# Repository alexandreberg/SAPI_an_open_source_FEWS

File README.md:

# SAPI — Sistema de Alerta Prévio de Inundações

**Flood Early Warning System** — a low-cost, open-source, LoRa-based platform for water-level
and rainfall monitoring, machine-learning flood forecasting and multi-channel alerts,
developed and validated as a Master's dissertation project (IFSC, Florianópolis, Brazil).

## Read this README in your language / Leia este README no seu idioma

| Language | File |
|----------|------|
| 🇬🇧 English | **[README-en.md](README-en.md)** |
| 🇧🇷 Português | **[README-pt.md](README-pt.md)** |

> **Note / Nota** — The code, comments and most technical documentation in this repository
> are in **English**; the README and some documents in `docs/` are also in **Portuguese**,
> the language of the dissertation.
>
> O código, os comentários e a maior parte da documentação técnica deste repositório estão
> em **inglês**; o README e alguns documentos em `docs/` estão também em **português**, o
> idioma da dissertação.

## Quick links / Links rápidos

- Releases (firmware, models, hardware, web interface):
  <https://github.com/alexandreberg/SAPI_an_open_source_FEWS/releases>
- Project specification / Especificação do projeto: [`docs/system-overview.md`](docs/system-overview.md)
- Changelog: [`CHANGELOG.md`](CHANGELOG.md)
- Predictive models / Modelos preditivos:
  [`predictive-models/`](predictive-models/README.md)
- How this repository was built / Como este repositório foi construído:
  [`docs/PROVENANCE.md`](docs/PROVENANCE.md)

## License / Licença

Software: [AGPL-3.0-or-later](LICENSE) · Hardware (`hardware/`):
[CERN-OHL-S-2.0](LICENSES/CERN-OHL-S-2.0.txt) · Third-party credits / Créditos: [`NOTICE`](NOTICE)

Copyright (C) 2024–2026 Alexandre Nuernberg.

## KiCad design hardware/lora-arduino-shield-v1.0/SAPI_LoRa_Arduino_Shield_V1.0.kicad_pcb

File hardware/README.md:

# Hardware — KiCad projects

KiCad 9 projects of the two custom shields used by the SAPI stations. Both are
fabrication-ready (gerbers in `gerber_to_order/`) and licensed under
[CERN-OHL-S-2.0](../LICENSES/CERN-OHL-S-2.0.txt).

| Project | Release | What it does |
|---------|---------|--------------|
| [`morpho-shield-v1.2/`](morpho-shield-v1.2/) | `shield-morpho-v1.2.0` | ST Morpho interface board: tipping-bucket rain-gauge pulse counting, serial and trigger/echo ultrasonic sensor interfaces (US-100, HC-SR04, AJ-SR04M), I²C sensor bus (SHT20, BMP280), ADC for solar-panel and battery voltages, ST-Link connector, switched 3.3 V/5 V rails, 5 spare GPIOs |
| [`lora-arduino-shield-v1.0/`](lora-arduino-shield-v1.0/) | `shield-lora-arduino-v1.0.0` | Arduino-footprint radio shield for RFM69HC and LilyGo LoRa32 modules (any frequency; SAPI uses 915 MHz), with a debug LED that can be disabled for low power, a reset button and reconfigurable GPIOs |

## Git LFS and the 3D models

The 3D models (`*.step`, `*.stp`, `*.stl`, `*.wrl`, and zipped models) are stored in
**Git LFS**, ~0.9 GB in total. To clone without them:

```bash
GIT_LFS_SKIP_SMUDGE=1 git clone https://github.com/alexandreberg/SAPI_an_open_source_FEWS.git
```

KiCad opens the projects without the models; only the 3D viewer needs them. Each release
also has the complete project, models included, as a `.tar.gz` attachment.

## Third-party content

The SAPI design files (schematics, layouts, gerbers, BOM) are the author's work. The
projects also contain material **not** authored here, which keeps its original terms and
is not covered by the CERN-OHL-S licence:

- **3D models** (80 files per project) downloaded from CAD-sharing sites — folders named
  `*.snapshot.N` follow their download naming — made in SolidWorks, CATIA, FreeCAD,
  PRO/ENGINEER, the ASCON kernel and KiCad StepUp. Among them: the STM32 BluePill model,
  BME280/BMP280 modules, an SW868 antenna, 2.54 mm jumpers and pin headers, tactile and
  push switches, an optocoupler.
- **Symbol and footprint libraries** from SnapEDA and Digi-Key (`Project_Libraries/`,
  `Libraries/`).
- **Datasheets** of the 74HC166, CD4020BC, CD4040BEE4 and TIL133
  (`morpho-shield-v1.2/datasheets/`).

Their licences were not individually verified. If you are a rights holder and want a file
removed, please open an issue.

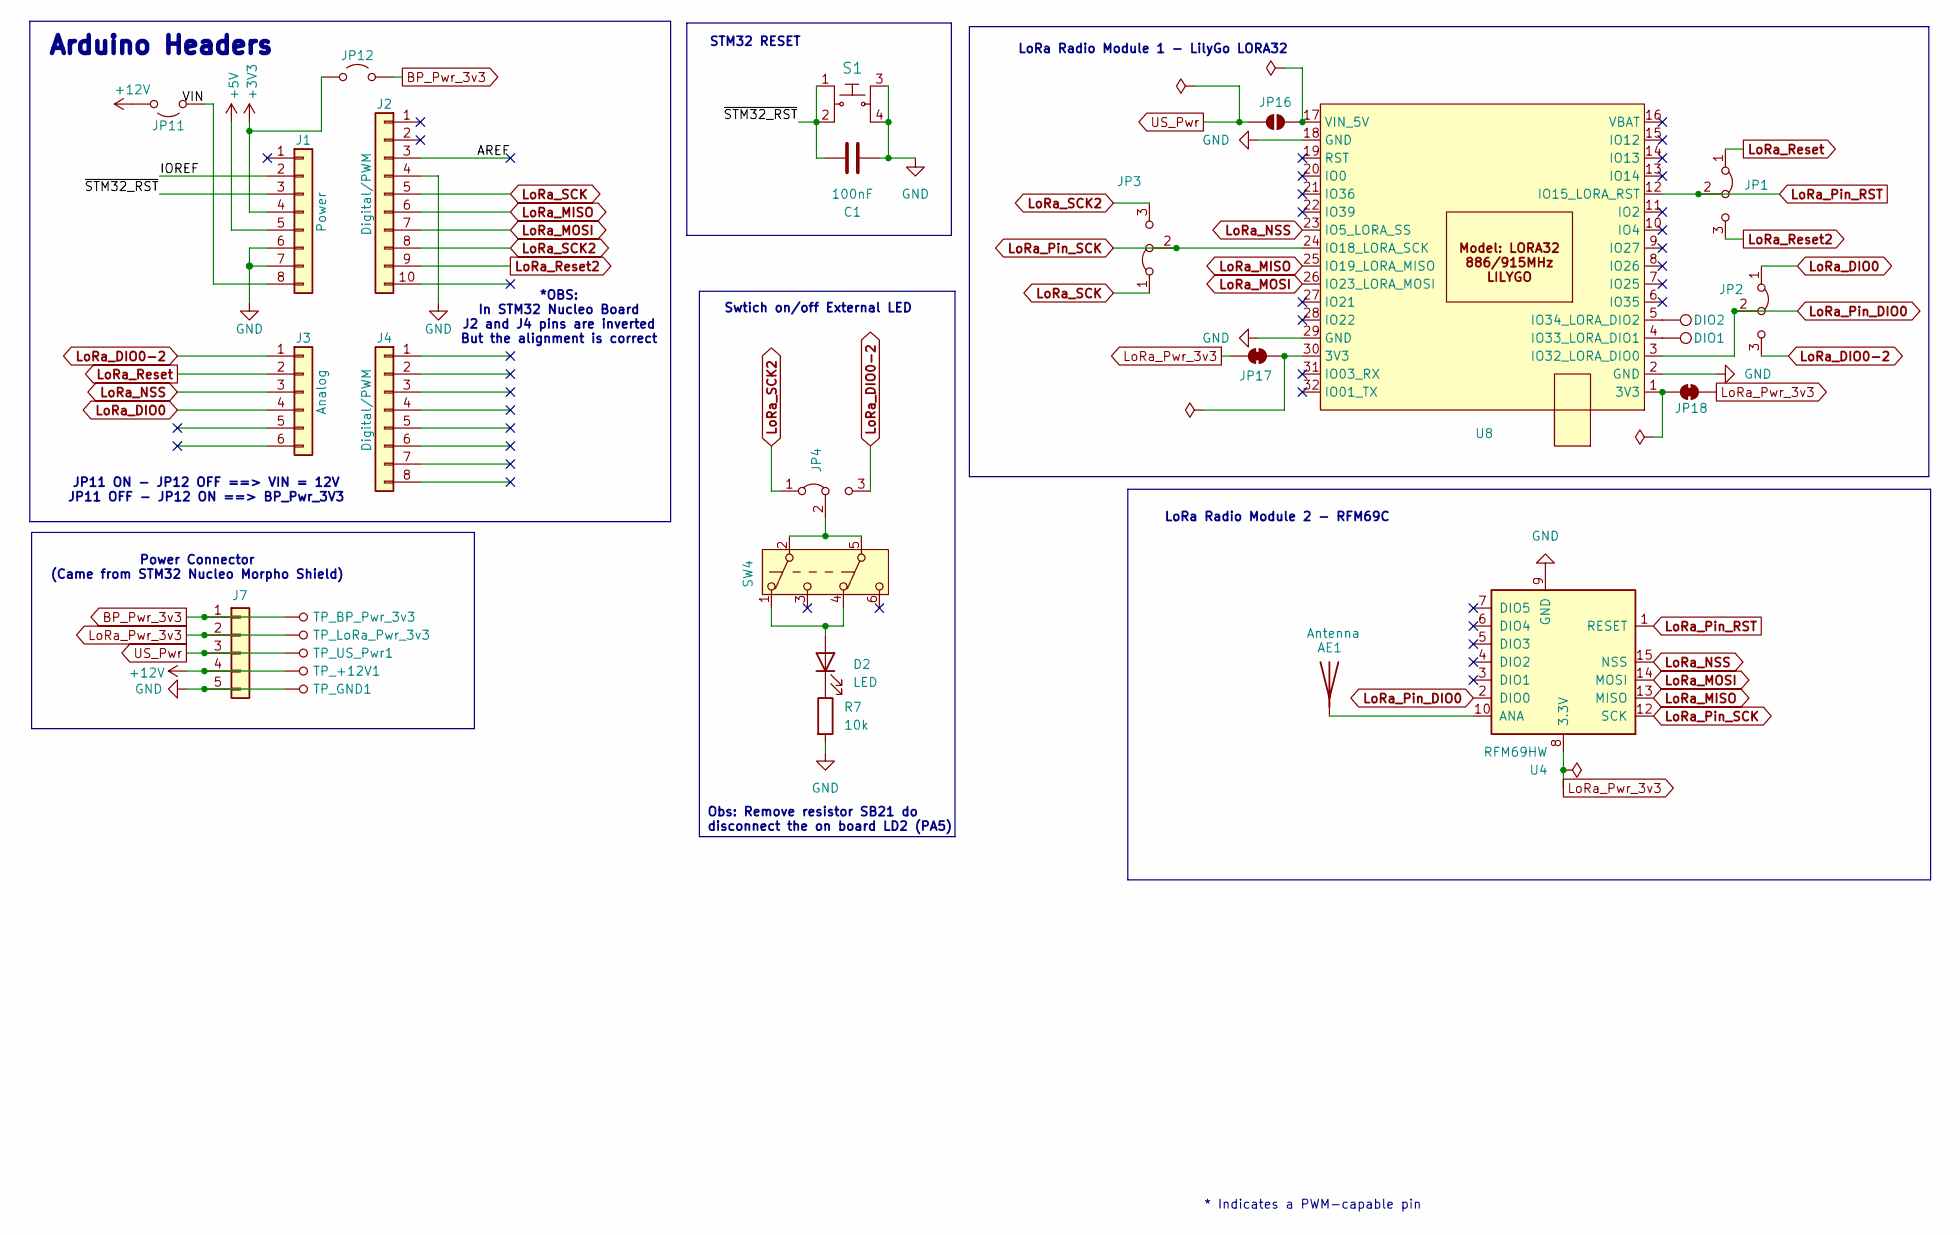
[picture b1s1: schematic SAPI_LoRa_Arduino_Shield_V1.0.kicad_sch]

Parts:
AE1: Antenna; ilha3d_LORA_Antenna
C1: 100nF; C_Disc_D5.1mm_W3.2mm_P5.00mm
D2: LED; LED_D3.0mm
J1: Power; PinHeader_1x08_P2.54mm_Vertical
J2: Digital/PWM; PinHeader_1x10_P2.54mm_Vertical
J3: Analog; PinHeader_1x06_P2.54mm_Vertical
J4: Digital/PWM; PinHeader_1x08_P2.54mm_Vertical
J7: Power; PinHeader_1x05_P2.54mm_Horizontal
JP1, JP4: LoRa_RST; Jumper_3Pins_SPDT_ilha3d
JP2: LoRa_DIO0; Jumper_3Pins_SPDT_ilha3d
JP3: LoRa_SCK; Jumper_3Pins_SPDT_ilha3d
JP11, JP12: Jumper_2_Open; PinHeader_1x02_P2.54mm_Vertical
JP16: SolderJumper_2_Open; SolderJumper-2_P1.3mm_Open_RoundedPad1.0x1.5mm
JP17, JP18: SolderJumper_2_Bridged; SolderJumper-2_P1.3mm_Bridged_RoundedPad1.0x1.5mm
R7: 10k; R_Axial_DIN0207_L6.3mm_D2.5mm_P7.62mm_Horizontal
S1: ilha3d_push_button_6x6; ilha3d_Switch_Tactile_THT_6x6mm; MPN 1825910-6; Digi-Key_PN 450-1650-ND
SW4: SW_Push_DPDT; SW_Push_2P2T_Toggle_CK_PVA2OAH5xxxxxxV2
TP21: DIO1; TestPoint_Pad_2.0x2.0mm
TP22: DIO2; TestPoint_Pad_2.0x2.0mm
TP_+12V1: +12V; Test_Point_D1.02mm; MPN 5000; Digi-Key_PN 36-5000-ND
TP_BP_Pwr_3v3: BP_Pwr_3v3; Test_Point_D1.02mm; MPN 5000; Digi-Key_PN 36-5000-ND
TP_GND1: GND; Test_Point_D1.02mm; MPN 5000; Digi-Key_PN 36-5000-ND
TP_LoRa_Pwr_3v3: LoRa_Pwr_3v3; Test_Point_D1.02mm; MPN 5000; Digi-Key_PN 36-5000-ND
TP_US_Pwr1: US_PwR; Test_Point_D1.02mm; MPN 5000; Digi-Key_PN 36-5000-ND
U4: RFM69HW; HOPERF_RFM69HW
U8: Ilha3d_LiLyGO_LORA32_LORA_XY

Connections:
+3V3: J1.4, JP12.1 (A)
+5V: J1.5
+12V: J7.4, JP11.2 (B), TP_+12V1.1
/ ~STM32_RST: C1.1, J1.3, S1.1, S1.2
/AREF: J2.3
/IOREF: J1.2
/VIN: J1.8, JP11.1 (A)
BP_Pwr_3v3: J7.1, JP12.2 (B), TP_BP_Pwr_3v3.1
GND: C1.2, J1.6, J1.7, J2.4, J7.5, R7.2, S1.3, S1.4, TP_GND1.1, U4.9 (GND), U4.11 (GND), U8.2 (GND), U8.18 (GND), U8.29 (GND)
LoRa_DIO0: J3.4, JP2.1 (A)
LoRa_DIO0-2: J3.1, JP2.3 (B), JP4.3 (B)
LoRa_MISO: J2.6, U4.13 (MISO), U8.25 (IO19_LORA_MISO)
LoRa_MOSI: J2.7, U4.14 (MOSI), U8.26 (IO23_LORA_MOSI)
LoRa_NSS: J3.3, U4.15 (NSS), U8.23 (IO5_LORA_SS)
LoRa_Pin_DIO0: JP2.2 (C), U4.2 (DIO0), U8.3 (IO32_LORA_DIO0)
LoRa_Pin_RST: JP1.2 (C), U4.1 (RESET), U8.12 (IO15_LORA_RST)
LoRa_Pin_SCK: JP3.2 (C), U4.12 (SCK), U8.24 (IO18_LORA_SCK)
LoRa_Pwr_3v3: J7.2, JP17.2 (B), JP18.1 (A), TP_LoRa_Pwr_3v3.1, U4.8 (3.3V)
LoRa_Reset: J3.2, JP1.1 (A)
LoRa_Reset2: J2.9, JP1.3 (B)
LoRa_SCK: J2.5, JP3.1 (A)
LoRa_SCK2: J2.8, JP3.3 (B), JP4.1 (A)
unnamed: AE1.1 (A), U4.10 (ANA)
unnamed: D2.2 (A), SW4.1 (A), SW4.4 (A)
unnamed: D2.1 (K), R7.1
unnamed: JP4.2 (C), SW4.2 (B), SW4.5 (B)
unnamed: JP16.1 (A), U8.17 (VIN_5V)
unnamed: JP17.1 (A), U8.30 (3V3)
unnamed: JP18.2 (B), U8.1 (3V3)
unnamed: TP21.1, U8.4 (IO33_LORA_DIO1)
unnamed: TP22.1, U8.5 (IO34_LORA_DIO2)
US_Pwr: J7.3, JP16.2 (B), TP_US_Pwr1.1

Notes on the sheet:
Obs: Remove resistor SB21 do disconnect the on board LD2 (PA5)
*OBS: In STM32 Nucleo Board J2 and J4 pins are inverted But the alignment is correct
Swtich on/off External LED
LoRa Radio Module 2 - RFM69C
Arduino Headers
JP11 ON - JP12 OFF ==> VIN = 12V JP11 OFF - JP12 ON ==> BP_Pwr_3V3
* Indicates a PWM-capable pin
LoRa Radio Module 1 - LilyGo LORA32
STM32 RESET
Power Connector (Came from STM32 Nucleo Morpho Shield)

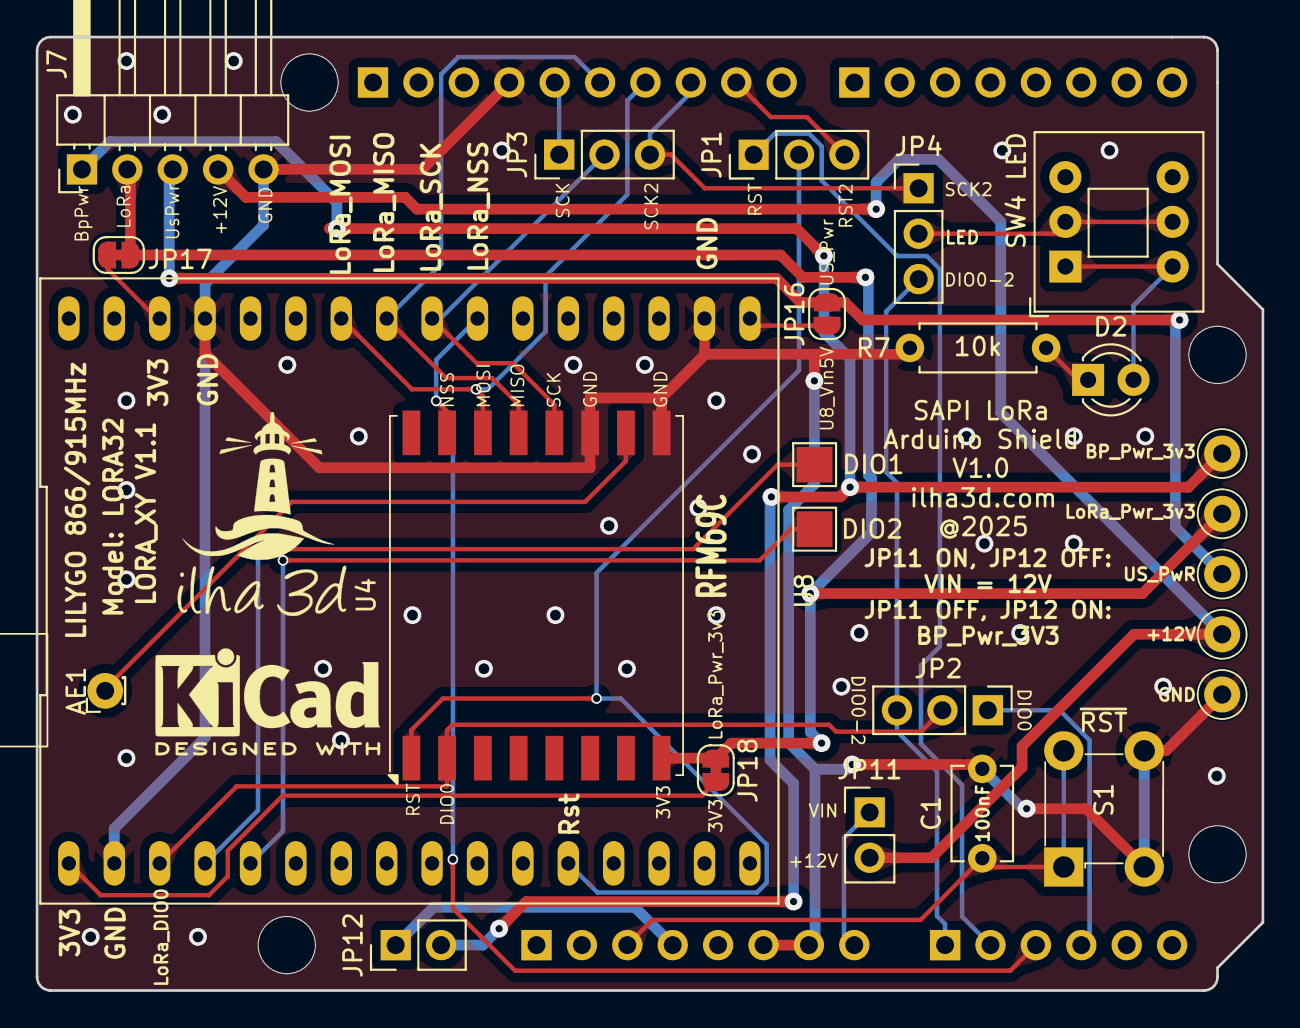
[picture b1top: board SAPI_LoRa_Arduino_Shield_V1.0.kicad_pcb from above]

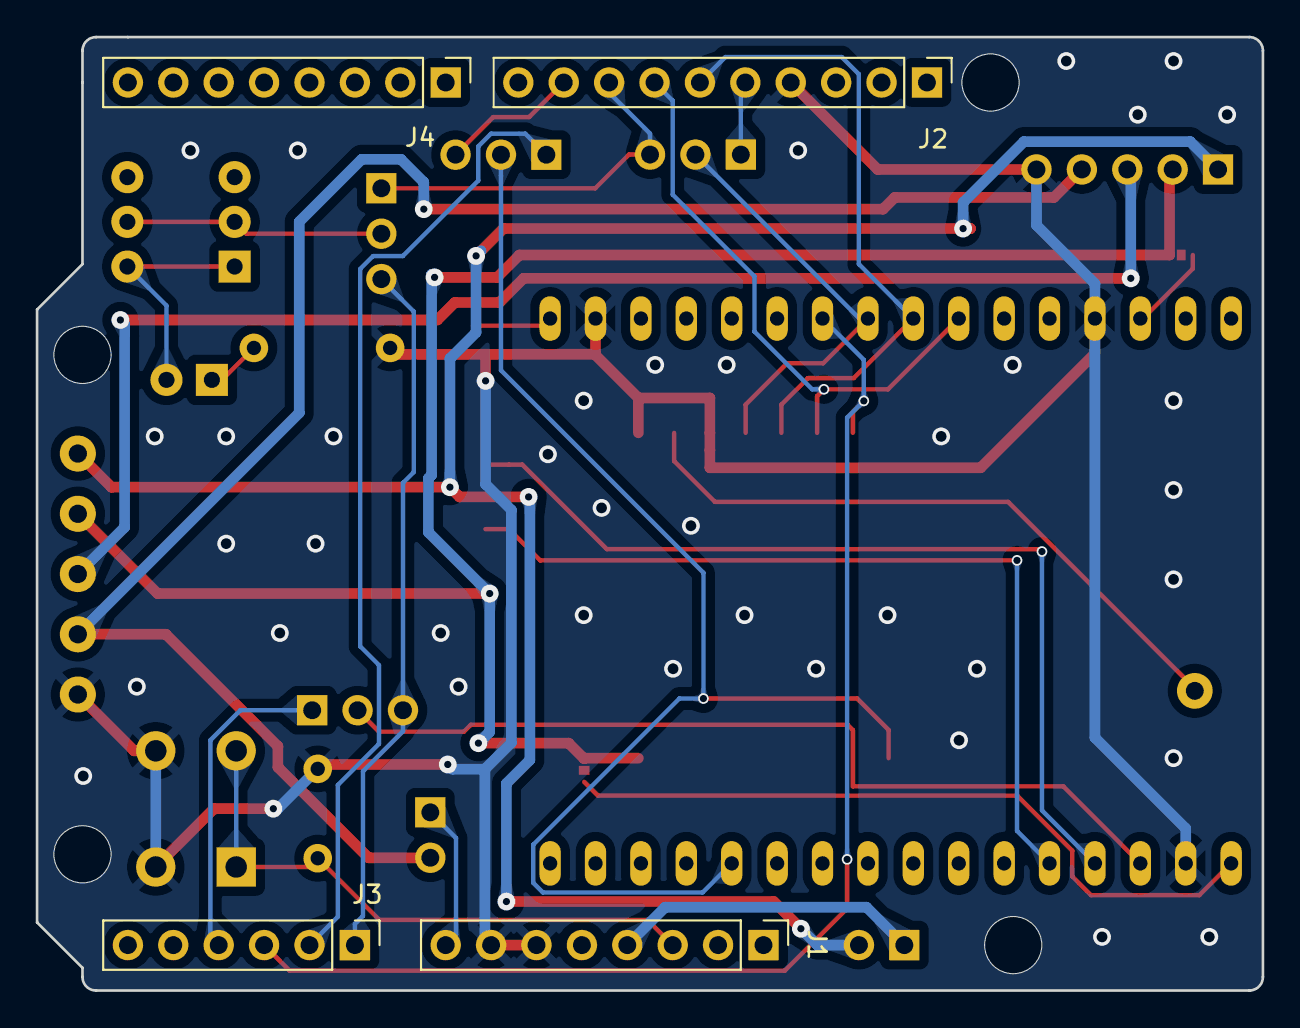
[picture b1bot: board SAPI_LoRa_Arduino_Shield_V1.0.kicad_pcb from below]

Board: 2 copper layers, 68.6 x 53.3 mm, 33 parts (4 on the bottom side), 29 nets.

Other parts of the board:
MH1, MH2, MH3, MH4: MountingHole_3.2mm

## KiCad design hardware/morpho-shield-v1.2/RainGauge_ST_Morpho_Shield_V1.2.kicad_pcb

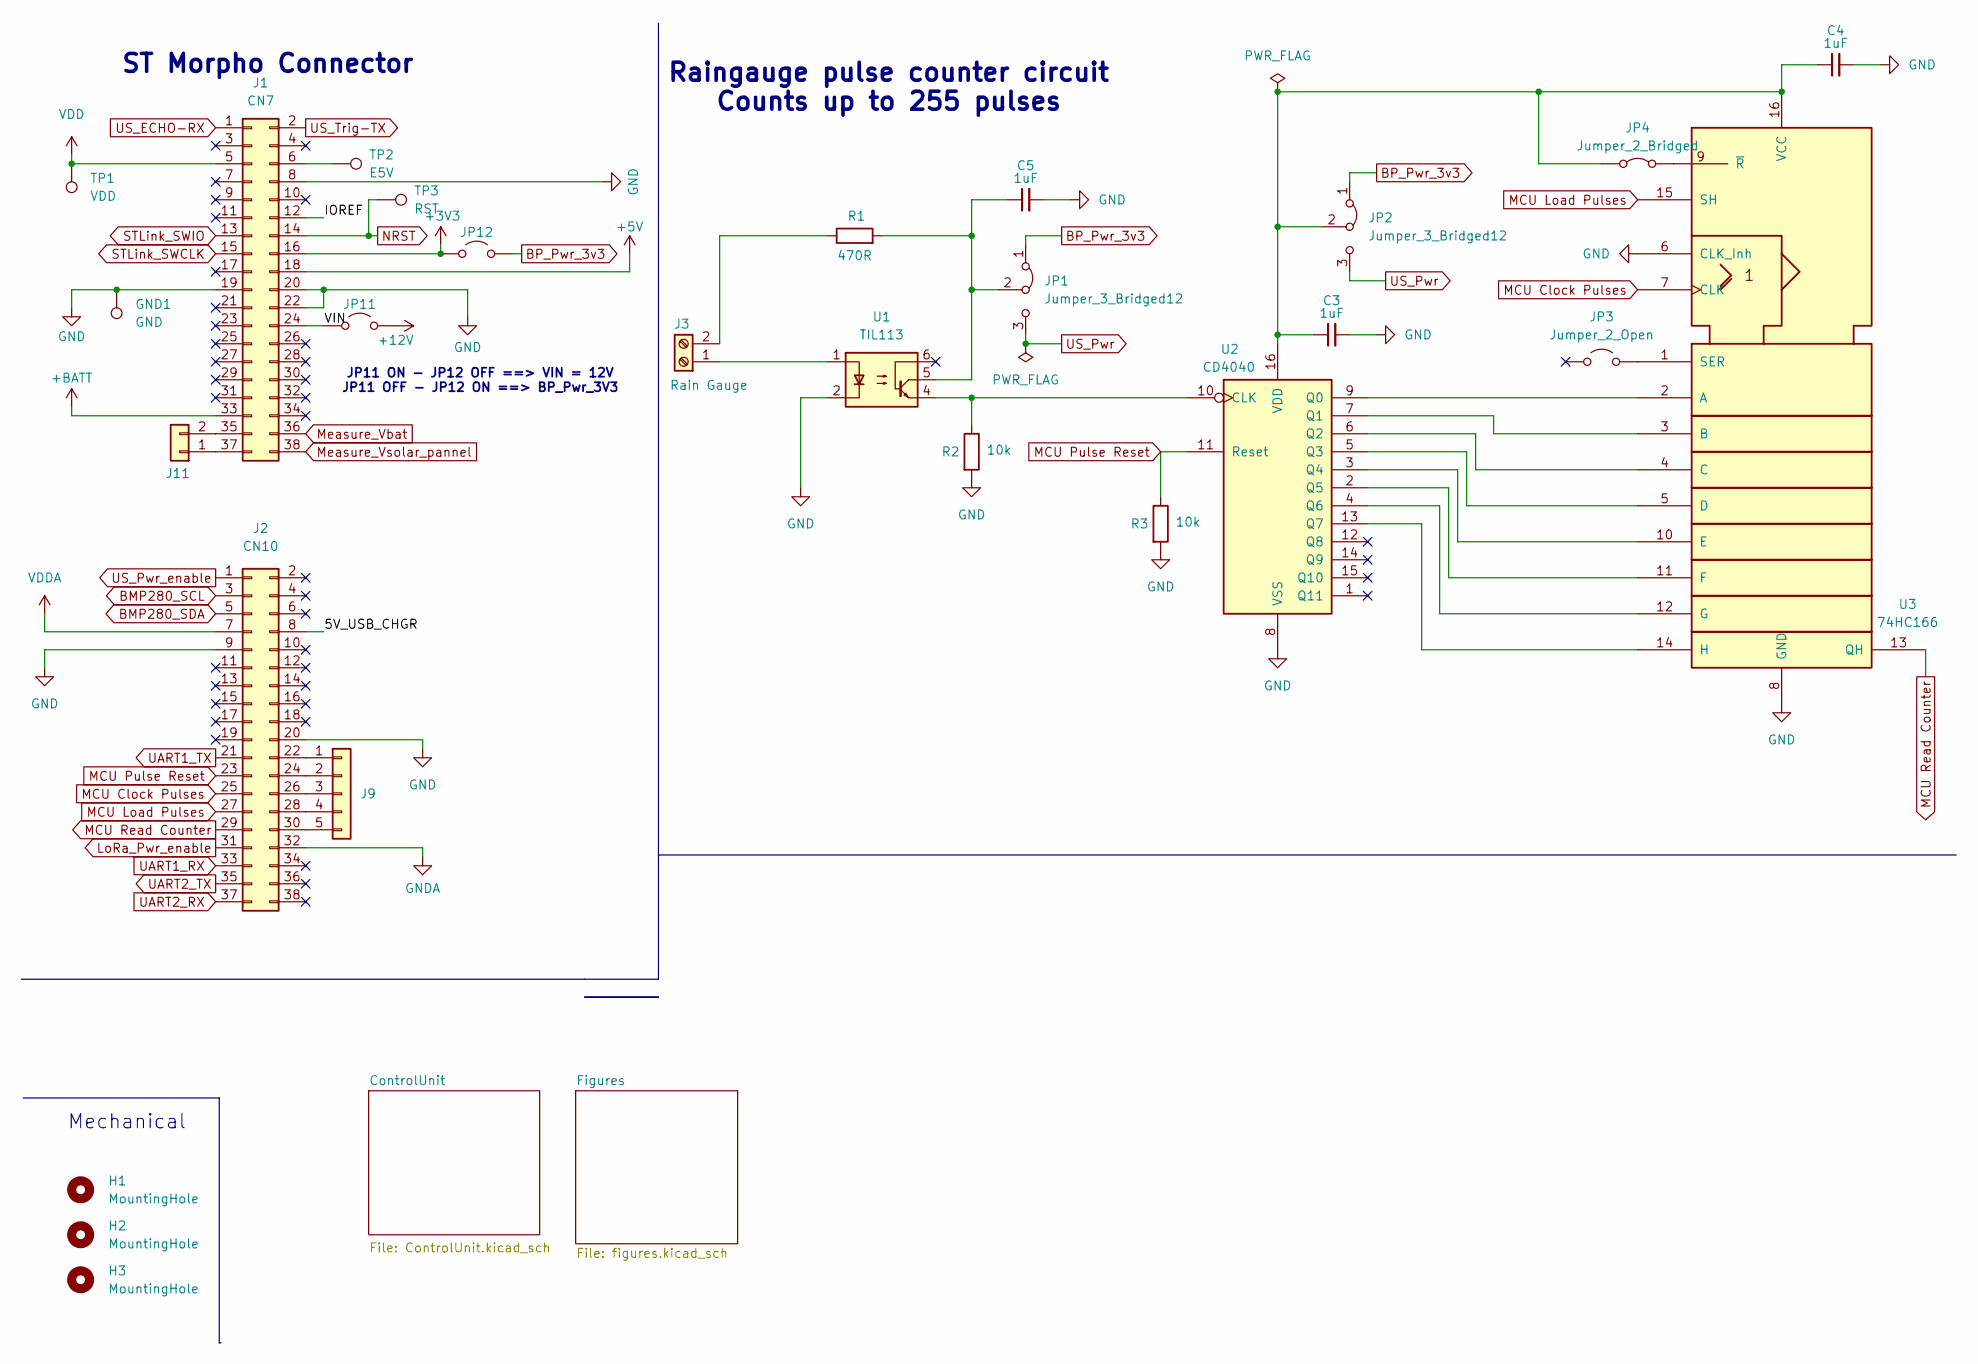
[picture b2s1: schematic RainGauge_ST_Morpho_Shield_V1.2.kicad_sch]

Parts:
C3, C4, C5: 1uF; C_Disc_D4.3mm_W1.9mm_P5.00mm
GND1: GND; PinHeader_1x01_P2.54mm_Vertical
H1, H2, H3: MountingHole; MountingHole_3.2mm_M3
J1: CN7; ilha3d_morphoPinSocket_2x19_P2.54mm_Vertical
J2: CN10; ilha3d_morphoPinSocket_2x19_P2.54mm_Vertical
J3: Rain Gauge; TerminalBlock_Phoenix_MKDS-1,5-2-5.08_1x02_P5.08mm_Horizont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
J9: Conn_01x05; PinHeader_1x05_P2.54mm_Vertical
J11: Conn_01x02; PinHeader_1x02_P2.54mm_Vertical
JP1, JP2: Jumper_3_Bridged12; Jumper_3Pins_SPDT_ilha3d
JP3, JP11, JP12: Jumper_2_Open; PinHeader_1x02_P2.54mm_Vertical
JP4: Jumper_2_Bridged; PinHeader_1x02_P2.54mm_Vertical
R1: 470R; R_Axial_DIN0207_L6.3mm_D2.5mm_P7.62mm_Horizontal
R2, R3: 10k; R_Axial_DIN0207_L6.3mm_D2.5mm_P7.62mm_Horizontal
TP1: VDD; PinHeader_1x01_P2.54mm_Vertical
TP2: E5V; PinHeader_1x01_P2.54mm_Vertical
TP3: RST; PinHeader_1x01_P2.54mm_Vertical
U1: TIL113; DIP-6_W7.62mm_Socket_LongPads
U2: CD4040; DIP-16_W7.62mm_Socket_LongPads
U3: 74HC166; DIP-16_W7.62mm_Socket_LongPads

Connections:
+3V3: J1.16, JP12.1 (A)
+5V: J1.18
+12V: JP11.2 (B); also elsewhere on the board
+BATT: J1.33
/5V_USB_CHGR: J2.8
/IOREF: J1.12
/VIN: J1.24, JP11.1 (A)
BMP280_SCL: J2.3; also elsewhere on the board
BMP280_SDA: J2.5; also elsewhere on the board
BP_Pwr_3v3: JP1.1 (A), JP2.1 (A), JP12.2 (B); also elsewhere on the board
GND: C3.2, C4.2, C5.2, GND1.1, J1.8, J1.19, J1.20, J1.22, J2.9, J2.20, R2.2, R3.2, U1.2, U2.8 (VSS), U3.6 (CLK_Inh), U3.8 (GND); also elsewhere on the board
GNDA: J2.32
LoRa_Pwr_enable: J2.31; also elsewhere on the board
MCU Clock Pulses: J2.25, U3.7 (CLK)
MCU Load Pulses: J2.27, U3.15 (SH)
MCU Pulse Reset: J2.23, R3.1, U2.11 (Reset)
MCU Read Counter: J2.29, U3.13 (QH)
Measure_Vbat: J1.36; also elsewhere on the board
Measure_Vsolar_pannel: J1.38; also elsewhere on the board
NRST: J1.14, TP3.1; also elsewhere on the board
unnamed: J1.6, TP2.1
unnamed: J1.35, J11.2
unnamed: J1.37, J11.1
unnamed: J2.22, J9.1
unnamed: J2.24, J9.2
unnamed: J2.26, J9.3
unnamed: J2.28, J9.4
unnamed: J2.30, J9.5
unnamed: J3.1, U1.1
unnamed: J3.2, R1.1
unnamed: C5.1, JP1.2 (C), R1.2, U1.5
unnamed: C3.1, C4.1, JP2.2 (C), JP4.1 (A), U2.16 (VDD), U3.16 (VCC)
unnamed: JP3.2 (B), U3.1 (SER)
unnamed: JP4.2 (B), U3.9 (~R)
unnamed: R2.1, U1.4, U2.10 (CLK)
unnamed: U2.9 (Q0), U3.2 (A)
unnamed: U2.7 (Q1), U3.3 (B)
unnamed: U2.6 (Q2), U3.4 (C)
unnamed: U2.5 (Q3), U3.5 (D)
unnamed: U2.3 (Q4), U3.10 (E)
unnamed: U2.2 (Q5), U3.11 (F)
unnamed: U2.4 (Q6), U3.12 (G)
unnamed: U2.13 (Q7), U3.14 (H)
STLink_SWCLK: J1.15; also elsewhere on the board
STLink_SWIO: J1.13; also elsewhere on the board
UART1_RX: J2.33
UART1_TX: J2.21
UART2_RX: J2.37; also elsewhere on the board
UART2_TX: J2.35; also elsewhere on the board
US_ECHO-RX: J1.1; also elsewhere on the board
US_Pwr: JP1.3 (B), JP2.3 (B); also elsewhere on the board
US_Pwr_enable: J2.1; also elsewhere on the board
US_Trig-TX: J1.2; also elsewhere on the board
VDD: J1.5, TP1.1
VDDA: J2.7

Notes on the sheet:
ST Morpho Connector
JP11 ON - JP12 OFF ==> VIN = 12V JP11 OFF - JP12 ON ==> BP_Pwr_3V3
Mechanical
Raingauge pulse counter circuit Counts up to 255 pulses

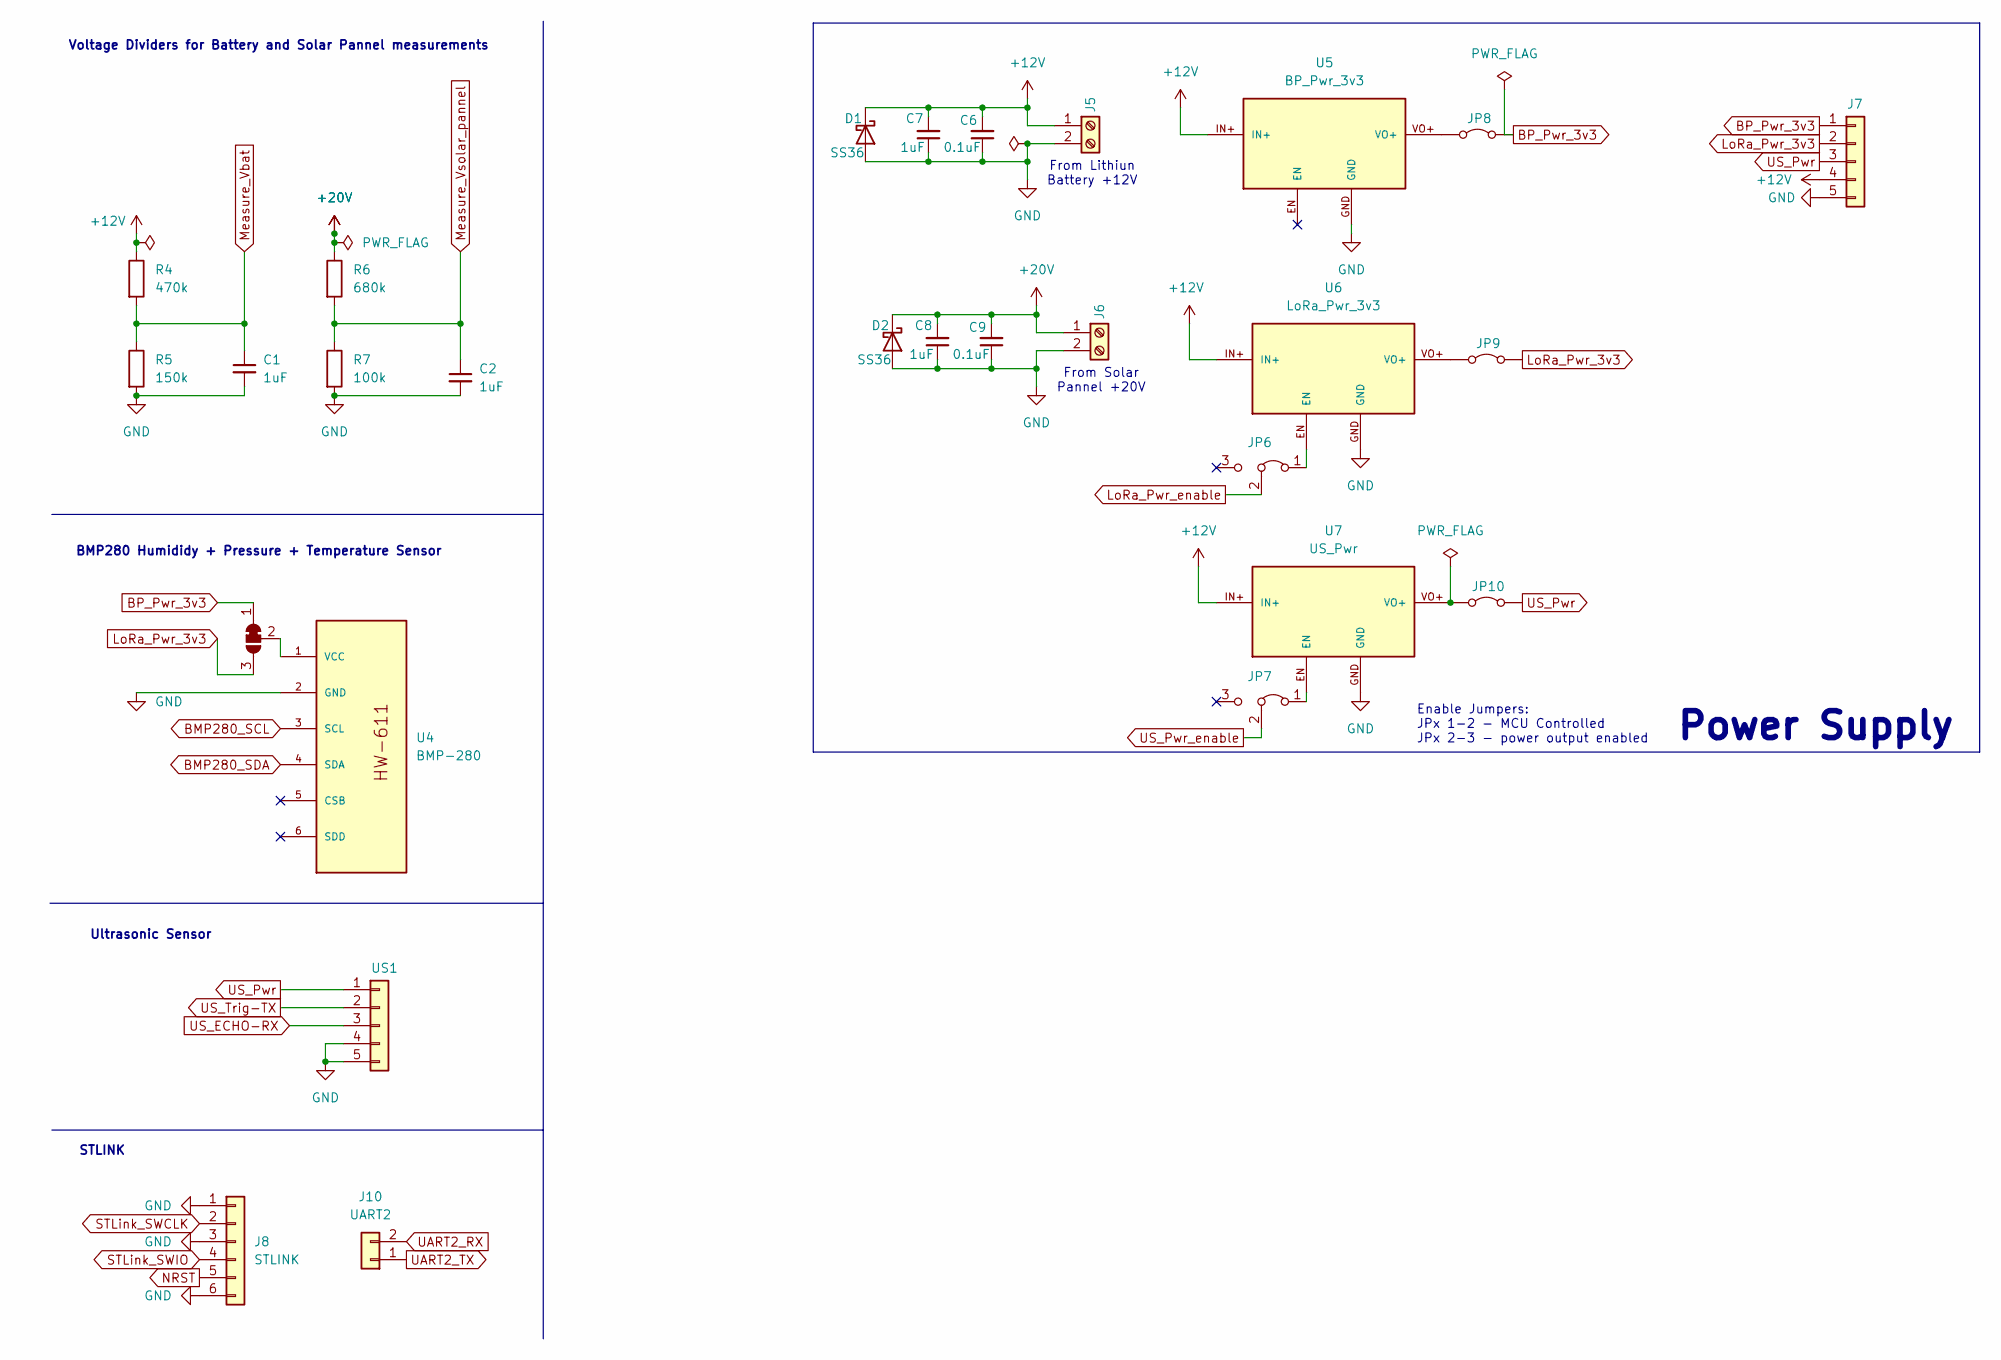
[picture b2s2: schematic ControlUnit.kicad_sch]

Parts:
C1, C2, C7, C8: 1uF; C_Disc_D4.3mm_W1.9mm_P5.00mm
C6, C9: 0.1uF; C_Disc_D4.3mm_W1.9mm_P5.00mm
D1, D2: SS36; D_SMA
J5: +12V; TerminalBlock_Phoenix_MKDS-1,5-2-5.08_1x02_P5.08mm_Horizont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
J6: +20V; TerminalBlock_Phoenix_MKDS-1,5-2-5.08_1x02_P5.08mm_Horizont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
J7: Power; PinHeader_1x05_P2.54mm_Horizontal
J8: STLINK; PinHeader_1x06_P2.54mm_Horizontal
J10: UART2; PinHeader_1x02_P2.54mm_Horizontal
JP5: SolderJumper_3_Bridged12; SolderJumper-3_P1.3mm_Bridged2Bar12_Pad1.0x1.5mm_NumberLabe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
JP6, JP7: PWR_EN; Jumper_3Pins_SPDT_ilha3d
JP8, JP9, JP10: Vout_ON; Ilha3d_Jumper_2Pins_closed
R4: 470k; R_Axial_DIN0207_L6.3mm_D2.5mm_P7.62mm_Horizontal
R5: 150k; R_Axial_DIN0207_L6.3mm_D2.5mm_P7.62mm_Horizontal
R6: 680k; R_Axial_DIN0207_L6.3mm_D2.5mm_P7.62mm_Horizontal
R7: 100k; R_Axial_DIN0207_L6.3mm_D2.5mm_P7.62mm_Horizontal
U4: BMP-280; PinHeader_1x06_P2.54mm_Horizontal
U5: BP_Pwr_3v3; HW-613
U6: LoRa_Pwr_3v3; HW-613
U7: US_Pwr; HW-613
US1: US; PinHeader_1x05_P2.54mm_Horizontal

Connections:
+12V: C6.2, C7.2, D1.1 (K), J5.1, J7.4, R4.1, U5.IN+, U6.IN+, U7.IN+; also elsewhere on the board
+20V: C8.2, C9.2, D2.1 (K), J6.1, R6.1
BMP280_SCL: U4.3 (SCL); also elsewhere on the board
BMP280_SDA: U4.4 (SDA); also elsewhere on the board
BP_Pwr_3v3: J7.1, JP5.1 (A), JP8.2 (B); also elsewhere on the board
GND: C1.2, C2.2, C6.1, C7.1, C8.1, C9.1, D1.2 (A), D2.2 (A), J5.2, J6.2, J7.5, J8.1, J8.3, J8.6, R5.2, R7.2, U4.2 (GND), U5.GND, U6.GND, U7.GND, US1.4, US1.5; also elsewhere on the board
LoRa_Pwr_3v3: J7.2, JP5.3 (B), JP9.2 (B)
LoRa_Pwr_enable: JP6.2 (C); also elsewhere on the board
Measure_Vbat: C1.1, R4.2, R5.1; also elsewhere on the board
Measure_Vsolar_pannel: C2.1, R6.2, R7.1; also elsewhere on the board
NRST: J8.5; also elsewhere on the board
unnamed: JP5.2 (C), U4.1 (VCC)
unnamed: JP6.1 (A), U6.EN
unnamed: JP7.1 (A), U7.EN
unnamed: JP8.1 (A), U5.VO+
unnamed: JP9.1 (A), U6.VO+
unnamed: JP10.1 (A), U7.VO+
STLink_SWCLK: J8.2; also elsewhere on the board
STLink_SWIO: J8.4; also elsewhere on the board
UART2_RX: J10.2; also elsewhere on the board
UART2_TX: J10.1; also elsewhere on the board
US_ECHO-RX: US1.3; also elsewhere on the board
US_Pwr: J7.3, JP10.2 (B), US1.1; also elsewhere on the board
US_Pwr_enable: JP7.2 (C); also elsewhere on the board
US_Trig-TX: US1.2; also elsewhere on the board

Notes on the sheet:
STLINK
From Lithiun Battery +12V
Enable Jumpers: JPx 1-2 - MCU Controlled JPx 2-3 - power output enabled
BMP280 Humididy + Pressure + Temperature Sensor
From Solar Pannel +20V
Voltage Dividers for Battery and Solar Pannel measurements
Power Supply
Ultrasonic Sensor

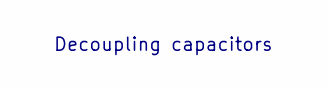
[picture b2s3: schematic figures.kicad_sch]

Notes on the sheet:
Decoupling capacitors

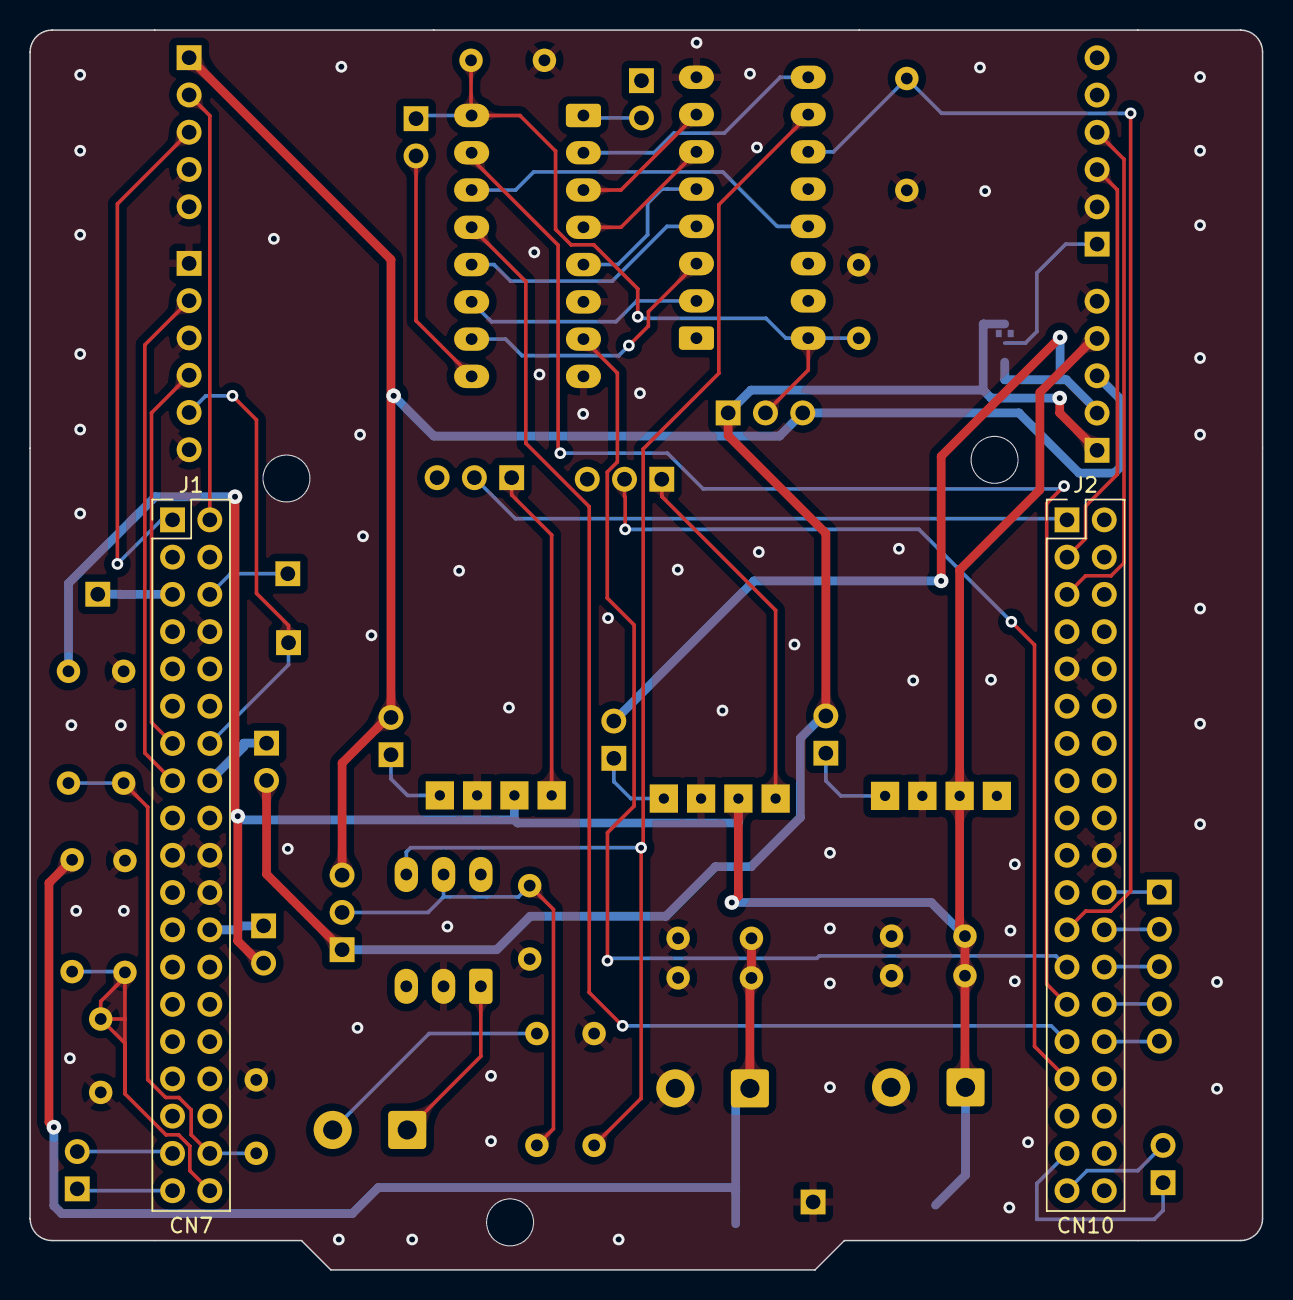
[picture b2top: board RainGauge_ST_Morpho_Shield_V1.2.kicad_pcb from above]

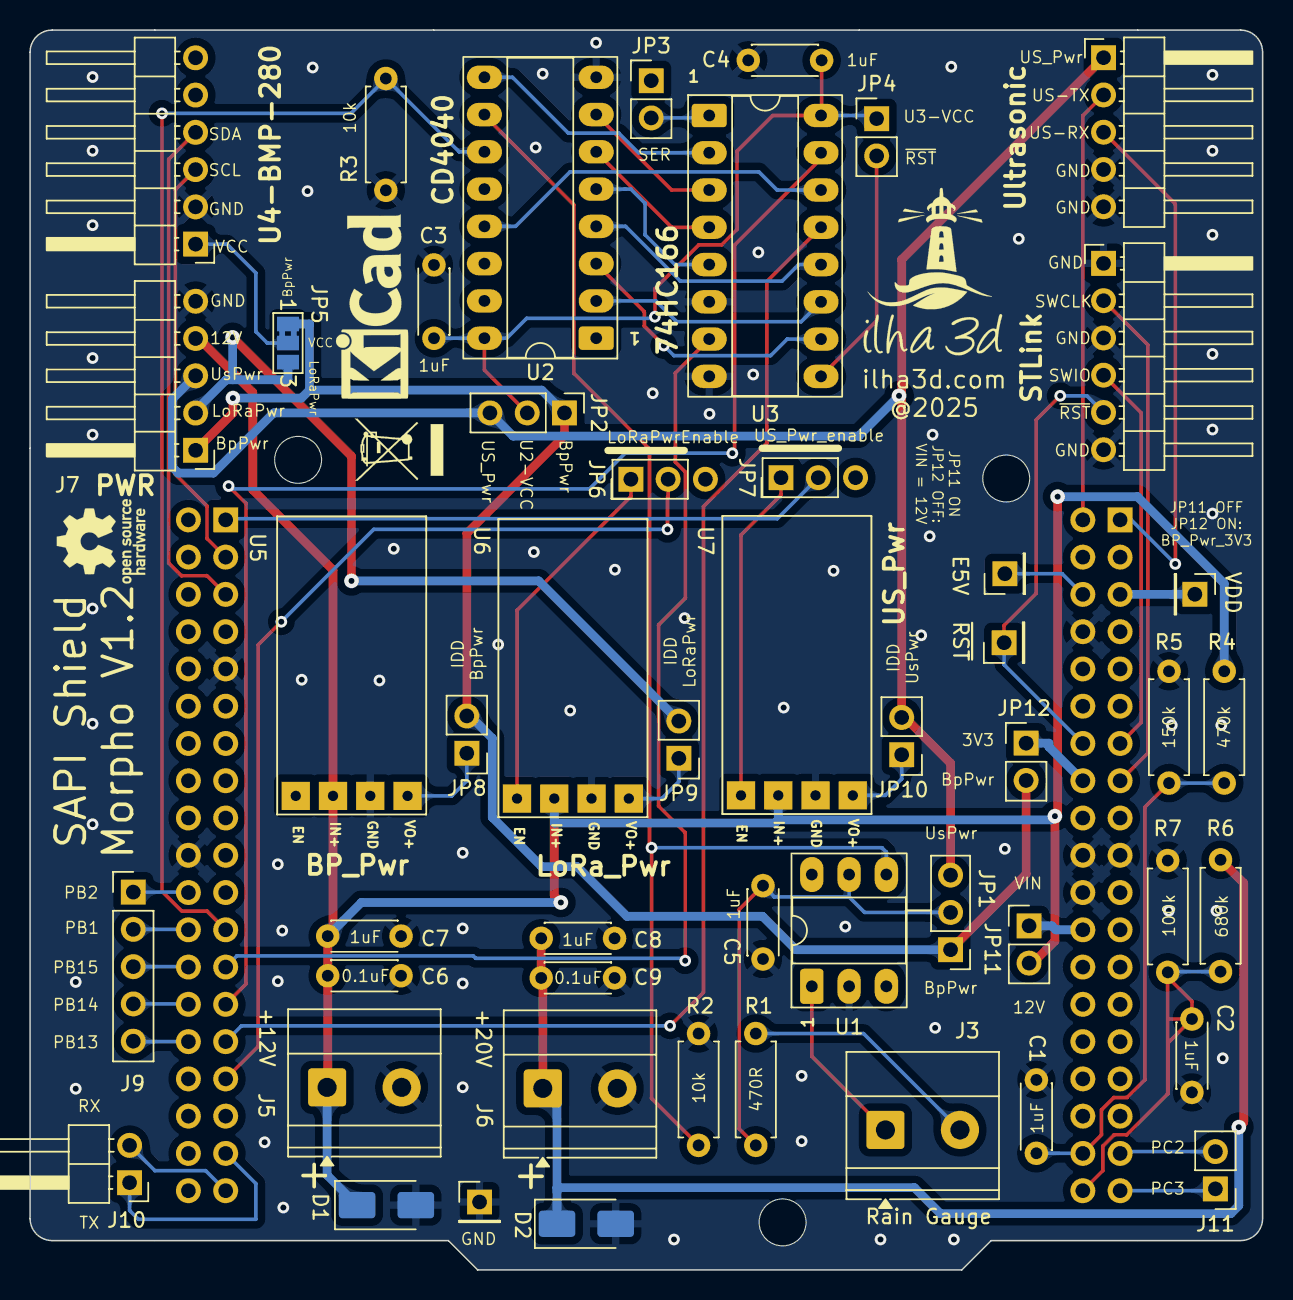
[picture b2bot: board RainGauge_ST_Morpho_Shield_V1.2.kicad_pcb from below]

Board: 2 copper layers, 84.0 x 84.5 mm, 59 parts (57 on the bottom side), 55 nets.

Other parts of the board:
Logo1: KiCad-Logo_5mm_SilkScreen
Logo2: WEEE-Logo_4.2x6mm_SilkScreen
Logo3: LOGO; logo ilha3d - 500x500 KiCad cheio_16.9mm_positive
Logo4: OSHW-Logo_5.7x6mm_SilkScreen

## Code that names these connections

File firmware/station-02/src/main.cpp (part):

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 * RFM95 LoRa Connection - STM32 Bluepill
 *    VCC - 3.3V
 *    GND - GND
 *    LoRa_SCK - LoRa_SCK (PA5)
 *    LoRa_MISO - LoRa_MISO (PA6)
 *    LoRa_MOSI - LoRa_MOSI (PA7)
 *    NSS - (PA4)
 *    RESET - (PA0)
 *    LoRa_DIO0 - (PA1)
 *
 * BackupRegisters:
 * See https://community.st.com/t5/stm32-mcus/how-to-use-the-stm32-s-backup-registers/ta-p/49892
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#define hibernation_time 880 // Hibernation time for deep sleep in seconds (15 min - 20 sec)

#ifdef enableWatchDog
#define ledPin PA0 // Choose LoRa_SCK2 (PB6) or LoRa_DIO_2 (PA0) - have to change jump (JP4) in the SAPI LoRA Arduino Shield  V1.0
#endif

#ifdef enableRTCstm32 // Working
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
#ifdef enableLoRa
// ================== LoRa Configuration Pins ==================
#define LoRa_SCK   PA5
#define LoRa_MISO  PA6
#define LoRa_MOSI  PA7
#define LoRa_NSS   PA4  // LoRa radio chip select
#define LoRa_RST   PA1  // LoRa radio reset
#define LoRa_DIO0  PB0  // Must be a hardware interrupt pin
#define LoRa_Pwr_enable PB3 // Enable LoRa power supply in the shield   

// Define LoRa Communication Band:
#define BAND 915E6 /*  915E6 for Brazil (902-928 MHz) \
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#endif

  // TODO: Enable the LoRa power supply HW-613 module
  // pinMode(LoRa_Pwr_enable, OUTPUT);
  // digitalWrite(LoRa_Pwr_enable, HIGH);

  delay(50); // delay for active the power supply
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  // LoRa.setTxPower(20); // Change LoRa transmission power to 20dBm
  // Serial.println("LoRa Power Trasnmission set to: 20dBm"); // ok 

  LoRa.setPins(LoRa_NSS, LoRa_RST, LoRa_DIO0); // SPI LoRa pins

  while (!LoRa.begin(BAND) && lora_startup_counter < 10)
  {
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

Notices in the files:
firmware/station-02/src/main.cpp:
SPDX-License-Identifier: AGPL-3.0-or-later
Copyright (C) 2024–2026 Alexandre Nuernberg <alexandreberg@gmail.com>
This program is free software: you can redistribute it and/or modify
it under the terms of the GNU Affero General Public License as published by
the Free Software Foundation, either version 3 of the License, or
(at your option) any later version.
